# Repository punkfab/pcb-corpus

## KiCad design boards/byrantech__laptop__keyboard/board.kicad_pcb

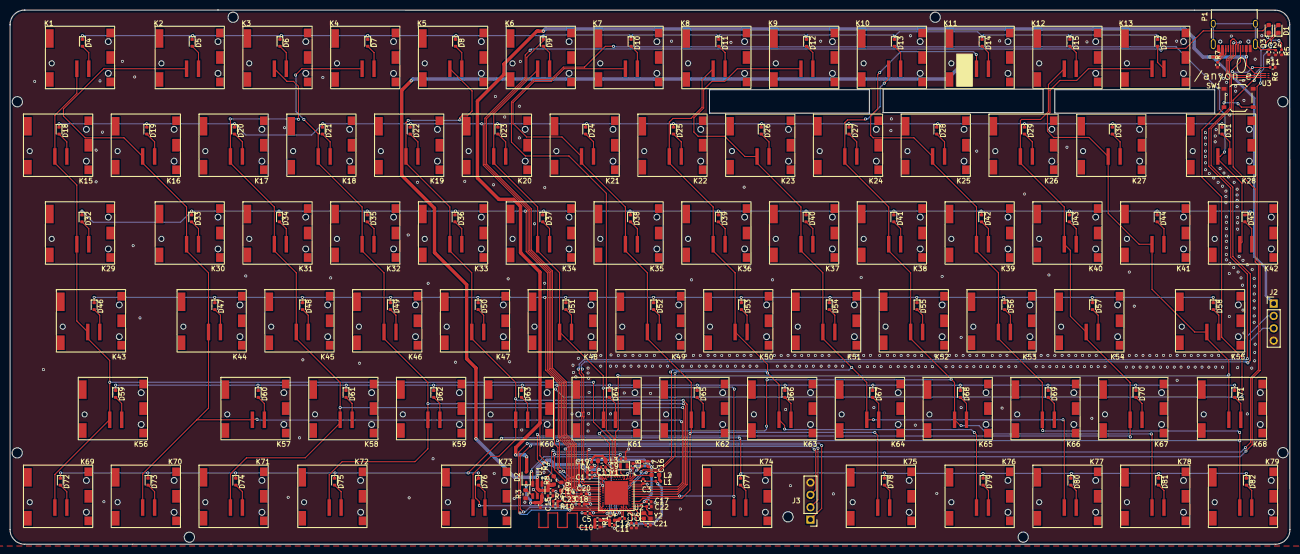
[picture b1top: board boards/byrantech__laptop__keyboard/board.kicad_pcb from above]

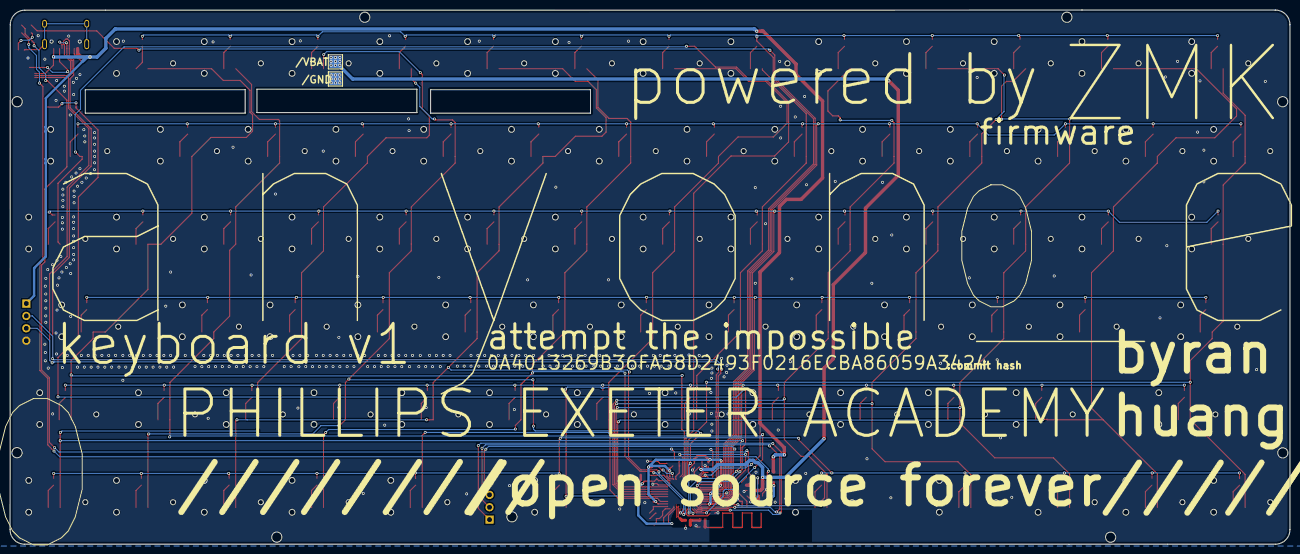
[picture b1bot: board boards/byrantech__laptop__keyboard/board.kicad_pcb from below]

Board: 2 copper layers, 262.5 x 109.5 mm, 220 parts (2 on the bottom side), 136 nets.

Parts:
AE1: Antenna; 2.4GHz-meander-antenna-v2
C1, C4, C13, C19: 4.7uF; C_0402_1005Metric
C2, C14, C15, C20: 1uF; C_0402_1005Metric
C3: 47nF; C_0402_1005Metric
C5: 1nF; C_0402_1005Metric
C6: 100pF; C_0402_1005Metric
C7, C16, C17, C18: 100nF; C_0402_1005Metric
C8, C9, C21, C22: 15pF; C_0402_1005Metric
C10: 1.5pF; C_0402_1005Metric
C11, C12: 1pF; C_0402_1005Metric
C23: 10nF; C_0402_1005Metric
C24: 1000pF/NC; C_0402_1005Metric
D1: CHG; LED_0603_1608Metric
D2: B5819W SL; D_SOD-323
D3: BLUE; LED_0603_1608Metric
D4, D5, D6, D7, D8, D9, D10, D11, D12, D13, D14, D15, D16, D18, D19, D20, D21, D22, D23, D24, D25, D26, D27, D28, D29, D30, D31, D32, D33, D34, D35, D36, D37, D38, D39, D40, D41, D42, D43, D44, D45, D46, D47, D48, D49, D50, D51, D52, D53, D54, D55, D56, D57, D58, D59, D60, D61, D62, D63, D64, D65, D66, D67, D68, D69, D70, D71, D72, D73, D74, D75, D76, D77, D78, D79, D80, D81, D82: D; D_SOD-523
H9, H10, H11, H13, H14, H16, H18, H20, H21: M2; M2_No_Padding
J2: USB POGO; PinHeader_1x04_P2.54mm_Vertical
J3: Debug; PinHeader_1x04_P2.54mm_Vertical
K1: Esc; Cherry_ULP_SMD
K2: F1; Cherry_ULP_SMD
K3: F2; Cherry_ULP_SMD
K4: F3; Cherry_ULP_SMD
K5: F4; Cherry_ULP_SMD
K6: F5; Cherry_ULP_SMD
K7: F6; Cherry_ULP_SMD
K8: F7; Cherry_ULP_SMD
K9: F8; Cherry_ULP_SMD
K10: F9; Cherry_ULP_SMD
K11: F10; Cherry_ULP_SMD
K12: F11; Cherry_ULP_SMD
K13: F12; Cherry_ULP_SMD
K15: ~~,`; Cherry_ULP_SMD
K16: !,1; Cherry_ULP_SMD
K17: @,2; Cherry_ULP_SMD
K18: #,3; Cherry_ULP_SMD
K19: $,4; Cherry_ULP_SMD
K20: %,5; Cherry_ULP_SMD
K21: ^,6; Cherry_ULP_SMD
K22: &,7; Cherry_ULP_SMD
K23: *,8; Cherry_ULP_SMD
K24: (,9; Cherry_ULP_SMD
K25: ),0; Cherry_ULP_SMD
K26: _,-; Cherry_ULP_SMD
K27: +,=; Cherry_ULP_SMD
K28: Backspace; Cherry_ULP_SMD
K29: Tab; Cherry_ULP_SMD
K30: Q; Cherry_ULP_SMD
K31: W; Cherry_ULP_SMD
K32: E; Cherry_ULP_SMD
K33: R; Cherry_ULP_SMD
K34: T; Cherry_ULP_SMD
K35: Y; Cherry_ULP_SMD
K36: U; Cherry_ULP_SMD
K37: I; Cherry_ULP_SMD
K38: O; Cherry_ULP_SMD
K39: P; Cherry_ULP_SMD
K40: {,[; Cherry_ULP_SMD
K41: },]; Cherry_ULP_SMD
K42: |,\; Cherry_ULP_SMD
K43: Caps Lock; Cherry_ULP_SMD
K44: A; Cherry_ULP_SMD
K45: S; Cherry_ULP_SMD
K46: D; Cherry_ULP_SMD
K47: F; Cherry_ULP_SMD
K48: G; Cherry_ULP_SMD
K49: H; Cherry_ULP_SMD
K50: J; Cherry_ULP_SMD
K51: K; Cherry_ULP_SMD
K52: L; Cherry_ULP_SMD
K53: :,;; Cherry_ULP_SMD
K54: ",'; Cherry_ULP_SMD
K55: Enter; Cherry_ULP_SMD
K56, K68: Shift; Cherry_ULP_SMD
K57: Z; Cherry_ULP_SMD
K58: X; Cherry_ULP_SMD
K59: C; Cherry_ULP_SMD
K60: V; Cherry_ULP_SMD
K61: B; Cherry_ULP_SMD
K62: N; Cherry_ULP_SMD
K63: M; Cherry_ULP_SMD
K64: <,,; Cherry_ULP_SMD
K65: >,.; Cherry_ULP_SMD
K66: ?,/; Cherry_ULP_SMD
K67: ↑; Cherry_ULP_SMD
K69: Fn; Cherry_ULP_SMD
K70: Ctrl; Cherry_ULP_SMD
K71, K76: Alt; Cherry_ULP_SMD
K72, K75: Meta; Cherry_ULP_SMD
K73, K74: Space; Cherry_ULP_SMD
K77: ←; Cherry_ULP_SMD
K78: ↓; Cherry_ULP_SMD
K79: →; Cherry_ULP_SMD
L1: 15nH; L_0402_1005Metric
L2, L3: 10uH; L_0603_1608Metric
L4: 3.9nH; L_0402_1005Metric
NT1: NetTie_2; net-tie-2-tiny
P1: USB-C; USB_C_Receptacle_HRO_TYPE-C-31-M-12
R1: 0R; R_0402_1005Metric
R2, R4: 10k; R_0402_1005Metric
R3: 2.7k; R_0603_1608Metric
R5: 1.5k; R_0402_1005Metric
R6, R7: 5.1k; R_0402_1005Metric
R8, R9: 2M; R_0603_1608Metric
R10: 10M; R_0402_1005Metric
R11: 1M; R_0402_1005Metric
SW1: Reset; SW_Push_1P1T_XKB_TS-1187A
TP5: VBAT; TestPoint_Pad_2.5x2.5mm
TP6: BAT GND; TestPoint_Pad_2.5x2.5mm
U1: BQ21040DBVR; SOT95P280X145-6N
U2: nRF52840; Nordic_AQFN-73-1EP_7x7mm_P0.5mm
U3: ESDR0502NMUTAG; UDFN-6_1.2x1.0mm_P0.4mm
Y1: 32.768 kHz; Crystal_SMD_2012-2Pin_2.0x1.2mm
Y2: 32MHz; Crystal_SMD_2016-4Pin_2.0x1.6mm

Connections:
/Key Matrix/Col_0: K1.1, K15.1, K29.1, K43.1, K56.1, K69.1, U2.U1 (TRACEDATA1/P0.12)
/Key Matrix/Col_1: K2.1, K16.1, K30.1, K44.1, K57.1, K70.1, U2.A8 (AIN7/P0.31)
/Key Matrix/Col_2: K3.1, K17.1, K31.1, K45.1, K58.1, K71.1, U2.A10 (AIN5/P0.29)
/Key Matrix/Col_3: K4.1, K18.1, K32.1, K46.1, K59.1, K72.1, U2.A12 (AIN0/P0.02)
/Key Matrix/Col_4: K5.1, K19.1, K33.1, K47.1, K60.1, K73.1, U2.A14 (P1.15)
/Key Matrix/Col_5: K6.1, K20.1, K34.1, K48.1, K61.1, K74.1, U2.A16 (P1.13)
/Key Matrix/Col_6: K7.1, K21.1, K35.1, K49.1, K62.1, K75.1, U2.A20 (P1.10)
/Key Matrix/Col_7: K8.1, K22.1, K36.1, K50.1, K63.1, K76.1, U2.J24 (NFC2/P0.10)
/Key Matrix/Col_8: K9.1, K23.1, K37.1, K51.1, K64.1, K77.1, U2.L24 (NFC1/P0.09)
/Key Matrix/Col_9: K10.1, K24.1, K38.1, K52.1, K65.1, K78.1, U2.R24 (P1.06)
/Key Matrix/Col_10: K11.1, K25.1, K39.1, K53.1, K66.1, K79.1, U2.U24 (P1.04)
/Key Matrix/Col_11: K12.1, K26.1, K40.1, K54.1, K67.1, U2.W24 (P1.02)
/Key Matrix/Col_12: K13.1, K27.1, K41.1, K55.1, K68.1, U2.L1 (P0.06)
/Key Matrix/Col_13: K28.1, K42.1, U2.N1 (P0.08)
/Key Matrix/Row_0: D4.1 (K), D5.1 (K), D6.1 (K), D7.1 (K), D8.1 (K), D9.1 (K), D10.1 (K), D11.1 (K), D12.1 (K), D13.1 (K), D14.1 (K), D15.1 (K), D16.1 (K), U2.AD8 (P0.13)
/Key Matrix/Row_1: D18.1 (K), D19.1 (K), D20.1 (K), D21.1 (K), D22.1 (K), D23.1 (K), D24.1 (K), D25.1 (K), D26.1 (K), D27.1 (K), D28.1 (K), D29.1 (K), D30.1 (K), D31.1 (K), U2.AD12 (P0.17)
/Key Matrix/Row_2: D32.1 (K), D33.1 (K), D34.1 (K), D35.1 (K), D36.1 (K), D37.1 (K), D38.1 (K), D39.1 (K), D40.1 (K), D41.1 (K), D42.1 (K), D43.1 (K), D44.1 (K), D45.1 (K), U2.AD16 (P0.20)
/Key Matrix/Row_3: D46.1 (K), D47.1 (K), D48.1 (K), D49.1 (K), D50.1 (K), D51.1 (K), D52.1 (K), D53.1 (K), D54.1 (K), D55.1 (K), D56.1 (K), D57.1 (K), D58.1 (K), U2.AD18 (P0.22)
/Key Matrix/Row_4: D59.1 (K), D60.1 (K), D61.1 (K), D62.1 (K), D63.1 (K), D64.1 (K), D65.1 (K), D66.1 (K), D67.1 (K), D68.1 (K), D69.1 (K), D70.1 (K), D71.1 (K), U2.AD20 (P0.24)
/Key Matrix/Row_5: D72.1 (K), D73.1 (K), D74.1 (K), D75.1 (K), D76.1 (K), D77.1 (K), D78.1 (K), D79.1 (K), D80.1 (K), D81.1 (K), D82.1 (K), U2.AC21 (P0.25)
/nRF52840/ANT: AE1.1 (A), C10.2, R1.2
/nRF52840/CC1: P1.A5 (CC), R6.1
/nRF52840/CC2: P1.B5 (VCONN), R7.1
BAT_VOLT: C23.2, R9.2, R10.1, U2.J1 (AIN2/P0.04)
BLUE_LED: D3.2 (A), U2.AD10 (P0.15)
GND: C1.1, C2.1, C3.1, C4.2, C5.2, C6.2, C7.2, C8.1, C9.1, C10.1, C11.1, C13.1, C14.2, C15.2, C16.1, C17.1, C18.1, C19.1, C20.1, C21.2, C22.2, C23.1, C24.2, J2.4, J3.4, NT1.2, P1.A1 (GND), P1.A12 (GND), P1.B1 (GND), P1.B12 (GND), R3.1, R4.1, R5.1, R6.2, R7.2, R10.2, R11.1, SW1.2, TP6.1, U1.5 (GND), U2.B7 (VSS), U2.EP (VSS), U3.1 (GND), Y2.2, Y2.4
unnamed: C11.2, L4.1, R1.1
unnamed: D1.2 (A), R2.2
unnamed: D1.1 (K), U1.3 (~CHG)
unnamed: C15.1, D2.1 (K), U1.6 (VIN)
unnamed: D3.1 (K), R5.2
unnamed: D4.2 (A), K1.2
unnamed: D5.2 (A), K2.2
unnamed: D6.2 (A), K3.2
unnamed: D7.2 (A), K4.2
unnamed: D8.2 (A), K5.2
unnamed: D9.2 (A), K6.2
unnamed: D10.2 (A), K7.2
unnamed: D11.2 (A), K8.2
unnamed: D12.2 (A), K9.2
unnamed: D13.2 (A), K10.2
unnamed: D14.2 (A), K11.2
unnamed: D15.2 (A), K12.2
unnamed: D16.2 (A), K13.2
unnamed: D18.2 (A), K15.2
unnamed: D19.2 (A), K16.2
unnamed: D20.2 (A), K17.2
unnamed: D21.2 (A), K18.2
unnamed: D22.2 (A), K19.2
unnamed: D23.2 (A), K20.2
unnamed: D24.2 (A), K21.2
unnamed: D25.2 (A), K22.2
unnamed: D26.2 (A), K23.2
unnamed: D27.2 (A), K24.2
unnamed: D28.2 (A), K25.2
unnamed: D29.2 (A), K26.2
unnamed: D30.2 (A), K27.2
unnamed: D31.2 (A), K28.2
unnamed: D32.2 (A), K29.2
unnamed: D33.2 (A), K30.2
unnamed: D34.2 (A), K31.2
unnamed: D35.2 (A), K32.2
unnamed: D36.2 (A), K33.2
unnamed: D37.2 (A), K34.2
unnamed: D38.2 (A), K35.2
unnamed: D39.2 (A), K36.2
unnamed: D40.2 (A), K37.2
unnamed: D41.2 (A), K38.2
unnamed: D42.2 (A), K39.2
unnamed: D43.2 (A), K40.2
unnamed: D44.2 (A), K41.2
unnamed: D45.2 (A), K42.2
unnamed: D46.2 (A), K43.2
unnamed: D47.2 (A), K44.2
unnamed: D48.2 (A), K45.2
unnamed: D49.2 (A), K46.2
unnamed: D50.2 (A), K47.2
unnamed: D51.2 (A), K48.2
unnamed: D52.2 (A), K49.2
unnamed: D53.2 (A), K50.2
unnamed: D54.2 (A), K51.2
unnamed: D55.2 (A), K52.2
unnamed: D56.2 (A), K53.2
unnamed: D57.2 (A), K54.2
unnamed: D58.2 (A), K55.2
unnamed: D59.2 (A), K56.2
unnamed: D60.2 (A), K57.2
unnamed: D61.2 (A), K58.2
unnamed: D62.2 (A), K59.2
unnamed: D63.2 (A), K60.2
unnamed: D64.2 (A), K61.2
unnamed: D65.2 (A), K62.2
unnamed: D66.2 (A), K63.2
unnamed: D67.2 (A), K64.2
unnamed: D68.2 (A), K65.2
unnamed: D69.2 (A), K66.2
unnamed: D70.2 (A), K67.2
unnamed: D71.2 (A), K68.2
unnamed: D72.2 (A), K69.2
unnamed: D73.2 (A), K70.2
unnamed: D74.2 (A), K71.2
unnamed: D75.2 (A), K72.2
unnamed: D76.2 (A), K73.2
unnamed: D77.2 (A), K74.2
unnamed: D78.2 (A), K75.2
unnamed: D79.2 (A), K76.2
unnamed: D80.2 (A), K77.2
unnamed: D81.2 (A), K78.2
unnamed: D82.2 (A), K79.2
unnamed: L1.2, L2.1
unnamed: C24.1, P1.S1 (SHIELD), R11.2
unnamed: R8.2, R9.1
unnamed: R3.2, U1.4 (ISET)
unnamed: R4.2, U1.1 (TS)
unnamed: C12.2, L4.2, U2.H23 (ANT)
unnamed: L2.2, U2.B3 (DCC)
unnamed: L3.2, U2.AB2 (DCCH)
unnamed: C7.1, U2.C1 (DEC1)
unnamed: C6.1, U2.D23 (DEC3)
unnamed: C2.2, C3.2, L1.1, U2.B5 (DEC4), U2.E24 (DEC6)
unnamed: C5.1, U2.N24 (DEC5)
unnamed: C4.1, U2.AC5 (DECUSB)
unnamed: C21.1, U2.B24 (XC1), Y2.1
unnamed: C22.1, U2.A23 (XC2), Y2.3
unnamed: C8.2, U2.D2 (XL1/P0.00), Y1.1
unnamed: C9.2, U2.F2 (XL2/P0.01), Y1.2
RESET: SW1.1, U2.AC9 (P0.14), U2.AC11 (P0.16), U2.AC13 (P0.18/~RESET)
SWC: J3.1, U2.AA24 (SWDCLK)
SWD: J3.2, U2.AC24 (SWDIO)
SWO: J3.3, U2.AD22 (TRACEDATA0/P1.00)
USB_D+: J2.2, P1.A6 (D+), P1.B6 (D+), U2.AD6 (D+), U3.5 (D+)
USB_D-: J2.3, P1.A7 (D-), P1.B7 (D-), U2.AD4 (D-), U3.6 (VBUS)
VBAT: C13.2, C14.1, R2.1, R8.1, TP5.1, U1.2 (OUT), U2.Y2 (VDDH)
VBUS: C1.2, D2.2 (A), J2.1, P1.A4 (VBUS), P1.A9 (VBUS), P1.B4 (VBUS), P1.B9 (VBUS), U2.AD2 (VBUS), U3.4 (D-)
VDD_NRF: C16.2, C17.2, C18.2, C19.2, C20.2, L3.1, U2.A22 (VDD), U2.AD14 (VDD), U2.AD23 (VDD), U2.B1 (VDD), U2.W1 (VDD)
VSS_PA: C12.1, NT1.1, U2.F23 (VSS_PA)

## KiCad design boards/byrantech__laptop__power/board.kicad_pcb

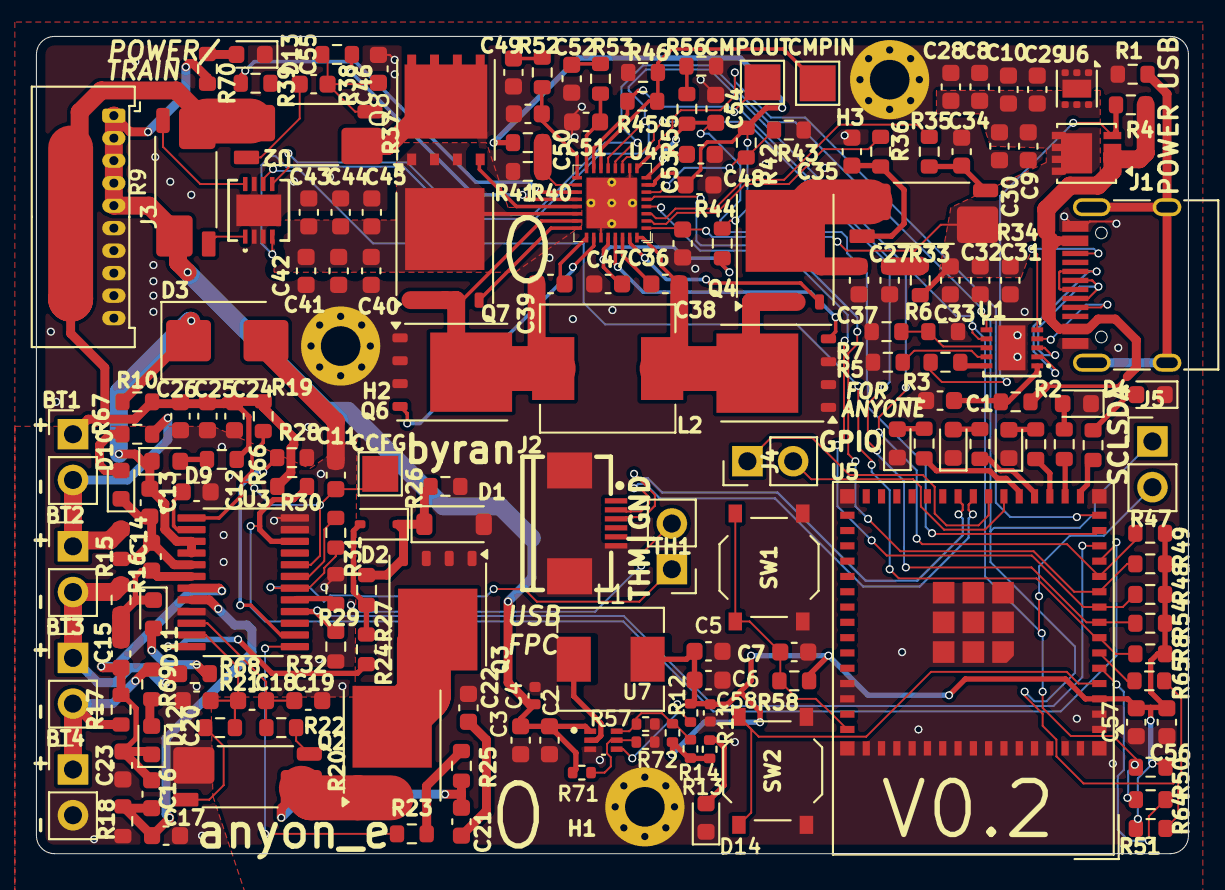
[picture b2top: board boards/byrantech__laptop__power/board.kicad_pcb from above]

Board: 13 copper layers, 64.0 x 45.4 mm, 179 parts (0 on the bottom side), 115 nets.

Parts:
BT1: Cell 1; PinHeader_1x02_P2.54mm_Vertical
BT2: Cell 2; PinHeader_1x02_P2.54mm_Vertical
BT3: Cell 3; PinHeader_1x02_P2.54mm_Vertical
BT4: Cell 4; PinHeader_1x02_P2.54mm_Vertical
C1, C7, C11, C12, C13, C14, C15, C16, C17, C23, C27, C46, C48: 1uF; C_0603_1608Metric
C2, C3, C8, C9, C24, C25, C28, C29, C30, C31, C32, C33, C40, C41, C42, C43, C44, C45, C56: 10uF; C_0603_1608Metric
C4, C58: 100nF; C_0402_1005Metric
C5, C6: 22uF; C_0603_1608Metric
C10, C26: 100nF; C_0603_1608Metric
C18, C19, C20, C21, C22, C55, C57: 0.1uF; C_0603_1608Metric
C34, C35: 33nF; C_0603_1608Metric
C36: 470nF; C_0603_1608Metric
C37: 10nF; C_0603_1608Metric
C38, C39: 47nF; C_0603_1608Metric
C47: 2.2uF; C_0603_1608Metric
C49: 680pF; C_0603_1608Metric
C50: 15pF; C_0603_1608Metric
C51: 33pF; C_0603_1608Metric
C52: 1800pF; C_0603_1608Metric
C53, C54: 100pF; C_0603_1608Metric
D1: MMSZ5248B; D_SOD-123
D2: BAS316; D_SOD-323
D3: SMBJ26A-13-F; D_SMB
D4: LED1; LED_0603_1608Metric
D5: LED2; LED_0603_1608Metric
D6: LED3; LED_0603_1608Metric
D7: LED4; LED_0603_1608Metric
D8: LED5; LED_0603_1608Metric
D9: C4 LED; LED_0603_1608Metric
D10: C3 LED; LED_0603_1608Metric
D11: C2 LED; LED_0603_1608Metric
D12: C1 LED; LED_0603_1608Metric
D13: VDD LED; LED_0603_1608Metric
D14: +3.3V LED; LED_0603_1608Metric
H1, H2, H3: M2; MountingHole_2.2mm_M2_Pad_Via
J1: USB-C Power + USB2.0; USB_C_Receptacle_HRO_TYPE-C-31-M-12
J2: USB; FPC-SMD_6P-P0.50_XUNPU_FPC-05F-6PH20
J3: BATTERY OUT; Molex_PicoBlade_53048-1010_1x10_P1.25mm_Horizontal
J4: BACKUP; PinHeader_1x02_P2.54mm_Vertical
J5: I2C; PinHeader_1x02_P2.54mm_Vertical
L1: MWSA0503S-3R3MT; L_Sunlord_MWSA0503S
L2: MWSA0603S-2R2MT; L_Sunlord_MWSA0603S
Q1: SI7617DN-T1-GE3; Vishay_PowerPAK_1212-8_Single
Q2, Q3, Q4, Q5, Q6, Q7: CSD18534Q5A; TDSON-8-1
Q8: AON6411; AO_DFN-8-1EP_5.55x5.2mm_P1.27mm_EP4.12x4.6mm
R1, R27: 1M; R_0603_1608Metric
R2, R38, R39, R44: 10R; R_0603_1608Metric
R3, R23, R24: 5.1k; R_0603_1608Metric
R4: 49.9k; R_0603_1608Metric
R5, R6: DNP; R_0603_1608Metric
R7, R64, R65: 0R; R_0603_1608Metric
R8: 2.2k; R_0603_1608Metric
R9, R34, R37: 10mΩ SHUNT FMF25FPJR010-LH; R_Shunt_Vishay_WSK2512_6332Metric_T1.19mm
R10, R15, R16, R17, R18: 33R; R_0603_1608Metric
R11, R71: 47k; R_0402_1005Metric
R12, R57: 10k; R_0402_1005Metric
R13: 49.9k; R_0402_1005Metric
R14: 510k; R_0402_1005Metric
R19, R66, R67, R68, R69, R70: 1k; R_0603_1608Metric
R20: 15mΩ SHUNT RLP25FEER015; R_Shunt_Vishay_WSK2512_6332Metric_T1.19mm
R21, R22: 100R; R_0603_1608Metric
R25: 10M; R_0603_1608Metric
R26: 3M; R_0603_1608Metric
R28, R41: 470k; R_0603_1608Metric
R29: 100k; R_0603_1608Metric
R30, R31, R32, R47, R48, R49, R50, R51, R52, R58, R59, R60, R61, R62, R63: 10k; R_0603_1608Metric
R33: 2.2R; R_0603_1608Metric
R35, R36: 5.1R; R_0603_1608Metric
R40: 130k; R_0603_1608Metric
R42: 390k; R_0603_1608Metric
R43: 220k; R_0603_1608Metric
R45: 2M; R_0603_1608Metric
R46: 300k; R_0603_1608Metric
R53: 40.2k; R_0603_1608Metric
R54: 200R; R_0603_1608Metric
R55: 110k; R_0603_1608Metric
R56: 27k; R_0603_1608Metric
R72: 12k; R_0402_1005Metric
SW1: RST; SW_Push_1P1T_XKB_TS-1187A
SW2: BOOT; SW_Push_1P1T_XKB_TS-1187A
TH1: 103AT 10k; PinHeader_1x02_P2.54mm_Vertical
TP1: CCFG; TestPoint_Pad_2.0x2.0mm
TP2: CMPIN; TestPoint_Pad_2.0x2.0mm
TP3: CMPOUT; TestPoint_Pad_2.0x2.0mm
U1: HUSB238; DFN-10_L3.0-W3.0-P0.50-BL-EP2.5
U2: LTC2943; DFN-8_DD_LIT
U3: BQ7791501PWR; SOP65P640X120-24N
U4: BQ25713RSNR; RSN0032B
U5: ESP32-S3-MINI-1; ESP32-S2-MINI-1
U6: TVS2200DRV; WSON-6-1EP_2x2mm_P0.65mm_EP1x1.6mm
U7: TPS564257DRLR; SOT50P160X60-6N

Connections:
+3.3V: C5.1, C6.1, C56.2, C57.2, C58.1, L1.2, R8.2, R11.2, R12.2, R13.2, R14.2, R47.2, R48.2, R49.2, R50.2, R51.2, R54.2, R58.2, U5.3 (3V3)
/3V3_SW: L1.1, U7.2 (SW)
/BATDRV_N: Q8.4 (G), U4.21 (BATDRV_N)
/BMS_SRN: C18.1, C20.1, R21.2, U3.11 (SRN)
/BMS_SRP: C18.2, C19.1, R22.2, U3.10 (SRP)
/BTST1: C38.2, U4.30 (BTST1)
/BTST2: C39.2, U4.25 (BTST2)
/C1: BT3.2 (-), BT4.1 (+), R17.1, R69.1
/C2: BT2.2 (-), BT3.1 (+), R16.1, R68.1
/C3: BT1.2 (-), BT2.1 (+), R15.1, R67.1
/C4: BT1.1 (+), C24.1, C25.1, C26.1, R9.4, R10.1, R19.1, R30.2, R37.1, R66.1
/CBI: R32.1, U3.16 (CBI), U5.13 (IO9)
/CC1: J1.A5 (CC1), U1.4 (CC1)
/CC2: J1.B5 (CC2), U1.5 (CC2)
/CELL_BATPRES: R40.1, R41.2, U4.18 (CELL_BATPRES)
/CHG: Q2.4 (G), R23.2, R25.2
/CHRG_OK: R48.1, U4.4 (CHRG_OK), U5.9 (IO5)
/CMPOUT: R45.2, R47.1, TP3.1, U4.15 (CMPOUT), U5.11 (IO7)
/COMP1: C51.1, R53.2, U4.16 (COMP1)
/COMP2: C50.1, R52.2, U4.17 (COMP2)
/D+: J1.A6 (D+), J1.B6 (D+), U1.2 (D+)
/D-: J1.A7 (D-), J1.B7 (D-), U1.3 (D-)
/DSG: D1.1 (K), D2.1 (K), Q3.4 (G), R26.2, R27.2
/EN: C7.2, R58.1, SW1.1 (A), U5.45 (EN)
/EN_OTG: R49.1, U4.5 (EN_OTG), U5.10 (IO6)
/HIDRV1: Q4.4 (G), U4.31 (HIDRV1)
/HIDRV2: Q7.4 (G), U4.24 (HIDRV2)
/IADPT: C54.2, R55.2, U4.8 (IADPT), U5.14 (IO10)
/IBAT: C53.2, U4.9 (IBAT), U5.15 (IO11)
/ILIM_HIZ: R42.1, R43.2, U4.6 (ILIM_HIZ)
/IO0: SW2.1 (A), U5.4 (IO0)
/LD: R28.2, U3.14 (LD)
/LED1: R59.1, U5.16 (IO12)
/LED2: R60.1, U5.17 (IO13)
/LED3: R61.1, U5.18 (IO14)
/LED4: R62.1, U5.19 (IO15)
/LED5: R63.1, U5.20 (IO16)
/LODRV1: Q5.4 (G), U4.29 (LODRV1)
/LODRV2: Q6.4 (G), U4.26 (LODRV2)
/PRES: R30.1, U3.22 (PRES), U5.12 (IO8)
/PROCHOT_N: R54.1, U4.11 (PROCHOT_N), U5.8 (IO4)
/REGN: C47.1, R44.2, U4.28 (REGN)
/SCL: J5.2, R50.1, R64.2, U1.7 (SCL), U2.4 (SCL), U4.13 (SCL)
/SDA: J5.1, R51.1, R65.2, U1.6 (SDA), U2.5 (SDA), U4.12 (SDA)
/SRN: R39.1, U4.19 (SRN)
/SRP: R38.1, U4.20 (SRP)
/SW1: C38.1, L2.1, Q4.1 (S), Q4.2 (S), Q4.3 (S), Q5.5 (D), U4.32 (SW1)
/SW2: C39.1, L2.2, Q6.5 (D), Q7.1 (S), Q7.2 (S), Q7.3 (S), U4.23 (SW2)
/USB_D+: J2.3, U5.24 (IO20)
/USB_D-: J2.2, U5.23 (IO19)
/VBUS: C8.1, C9.1, C10.1, C28.1, C29.1, C30.1, C31.1, C32.1, C33.1, C36.1, Q1.5 (D), R33.2, R34.4, U4.1 (VBUS), U6.4 (IN), U6.5 (IN), U6.6 (IN)
/VC0: C16.2, C17.1, R18.2, U3.8 (VC0)
/VC1: C15.2, C16.1, C23.1, D12.1 (K), R17.2, U3.7 (VC1)
/VC2: C14.2, C15.1, D11.1 (K), R16.2, U3.6 (VC2)
/VC3: C13.2, C14.1, D10.1 (K), R15.2, U3.5 (VC3)
/VC4: C13.1, D3.1 (A1), D9.1 (K), R10.2, U3.3 (VC5), U3.4 (VC4)
/VDDA: C48.1, R40.2, R42.2, R44.1, U4.7 (VDDA)
/VSYS: C40.1, C41.1, C42.1, C43.1, C44.1, C45.1, Q7.5 (D), Q8.1 (S), Q8.2 (S), Q8.3 (S), U4.22 (VSYS)
/~ALCC: R8.1, U2.6 (*ALCC), U5.7 (IO3)
GND: C1.2, C2.2, C3.2, C4.2, C5.2, C6.2, C7.1, C8.2, C9.2, C10.2, C22.2, C27.2, C28.2, C29.2, C30.2, C31.2, C32.2, C33.2, C34.2, C35.2, C36.2, C37.2, C40.2, C41.2, C42.2, C43.2, C44.2, C45.2, C46.2, C47.2, C48.2, C49.2, C50.2, C51.2, C52.2, C53.1, C54.1, C56.1, C57.1, C58.2, D1.2 (A), D4.1 (K), D5.1 (K), D6.1 (K), D7.1 (K), D8.1 (K), D13.1 (K), D14.1 (K), H1.1, H2.1, H3.1, J1.A1 (GND), J1.A12 (GND), J1.B1 (GND), J1.B12 (GND), J2.6, J2.MP (MountPin), J3.6, J3.7, J3.8, J3.9, J3.10, Q3.1 (S), Q3.2 (S), Q3.3 (S), Q5.1 (S), Q5.2 (S), Q5.3 (S), Q6.1 (S), Q6.2 (S), Q6.3 (S), R1.2, R5.2, R6.2, R7.2, R26.1, R28.1, R41.1, R43.1, R46.1, R56.1, R57.1, R72.1, SW1.2 (B), SW2.2 (B), U1.11 (GND), U2.2 (GND), U2.3 (GND), U2.7 (GND), U2.9 (EPAD), U4.10 (PSYS), U4.27 (PGND), U4.33 (PAD), U5.1 (GND), U5.2 (GND), U5.42 (GND), U5.43 (GND), U5.46 (GND), U5.47 (GND), U5.48 (GND), U5.49 (GND), U5.50 (GND), U5.51 (GND), U5.52 (GND), U5.53 (GND), U5.54 (GND), U5.55 (GND), U5.56 (GND), U5.57 (GND), U5.58 (GND), U5.59 (GND), U5.60 (GND), U5.61 (GND), U5.62 (GND), U5.63 (GND), U5.64 (GND), U5.65 (GND), U6.1 (GND), U6.2 (GND), U6.3 (GND), U6.7 (GND), U7.3 (GND)
GNDPWR: BT4.2 (-), C11.2, C12.2, C17.2, C19.2, C20.2, C23.2, C24.2, C25.2, C26.2, D3.2 (A2), R18.1, R20.1, R29.2, R32.2, TH1.2, U3.9 (VSS), U3.23 (CTRC), U3.24 (CTRD)
unnamed: C21.1, Q2.1 (S), Q2.2 (S), Q2.3 (S), R20.4, R25.1
unnamed: C21.2, C22.1
unnamed: C27.1, R33.1
unnamed: C34.1, R34.3, R35.2
unnamed: C35.1, R34.2, R36.2
unnamed: C46.1, C55.1, R37.3, R38.2
unnamed: C49.1, R52.1
unnamed: C52.1, R53.1
unnamed: C55.2, R37.2, R39.2
unnamed: D2.2 (A), R24.2, R27.1
unnamed: D4.2 (A), R59.2
unnamed: D5.2 (A), R60.2
unnamed: D6.2 (A), R61.2
unnamed: D7.2 (A), R62.2
unnamed: D8.2 (A), R63.2
unnamed: D9.2 (A), R66.2
unnamed: D10.2 (A), R67.2
unnamed: D11.2 (A), R68.2
unnamed: D12.2 (A), R69.2
unnamed: D13.2 (A), R70.2
unnamed: D14.2 (A), R11.1
unnamed: J1.S1 (SHIELD), R1.1
unnamed: J1.A4 (VBUS), J1.A9 (VBUS), J1.B4 (VBUS), J1.B9 (VBUS), Q1.1 (S), Q1.2 (S), Q1.3 (S), R2.1, R4.2
unnamed: J4.1, U5.22 (IO18)
unnamed: J4.2, U5.21 (IO17)
unnamed: Q1.4 (G), R3.2, R4.1
unnamed: Q2.5 (D), Q3.5 (D)
unnamed: C37.1, Q4.5 (D), R34.1
unnamed: Q8.5 (D), R37.4
unnamed: R20.2, R21.1
unnamed: R20.3, R22.1
unnamed: R55.1, R56.2
unnamed: R3.1, U1.10 (GATE)
unnamed: R5.1, U1.9 (ISET)
unnamed: C1.1, R2.2, U1.1 (VIN)
unnamed: R6.1, R7.1, U1.8 (VSET)
unnamed: R9.2, U2.1 (SENSE+)
unnamed: R9.3, U2.8 (SENSE-)
unnamed: C12.1, U3.2 (AVDD)
unnamed: C11.1, R19.2, TP1.1, U3.1 (VDD), U3.20 (CCFG)
unnamed: R23.1, U3.13 (CHG)
unnamed: R24.1, U3.12 (DSG)
unnamed: R29.1, U3.17 (OCDP)
unnamed: R31.2, TH1.1, U3.18 (TS)
unnamed: R31.1, U3.19 (VTB)
unnamed: R36.1, U4.2 (ACN)
unnamed: R35.1, U4.3 (ACP)
unnamed: R45.1, R46.2, TP2.1, U4.14 (CMPIN)
unnamed: R64.1, U5.5 (IO1)
unnamed: R65.1, U5.6 (IO2)
unnamed: R71.1, R72.2, U7.5 (EN)
unnamed: R13.1, R14.1, R57.2, U7.6 (FB)
unnamed: R12.1, U7.4 (PG)
VDD: C2.1, C3.1, C4.1, J3.1, J3.2, J3.3, J3.4, J3.5, R9.1, R70.1, R71.2, U7.1 (VIN)

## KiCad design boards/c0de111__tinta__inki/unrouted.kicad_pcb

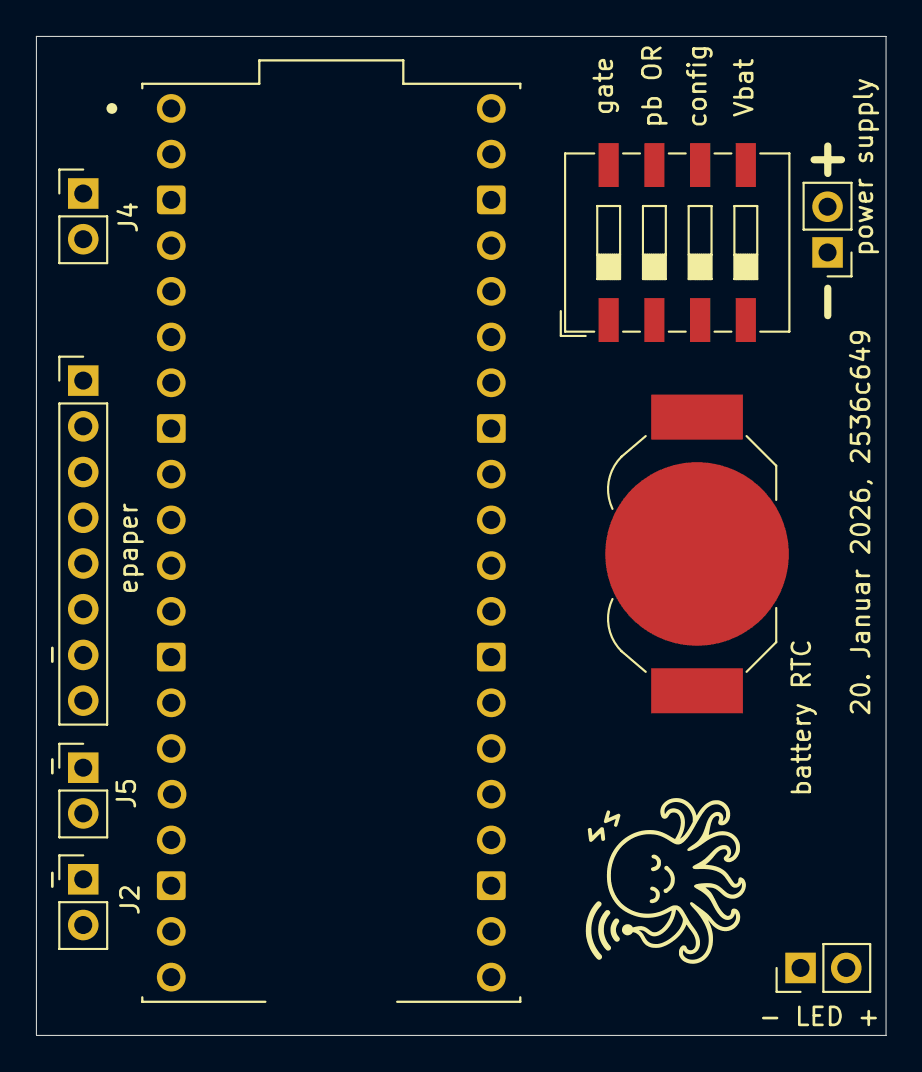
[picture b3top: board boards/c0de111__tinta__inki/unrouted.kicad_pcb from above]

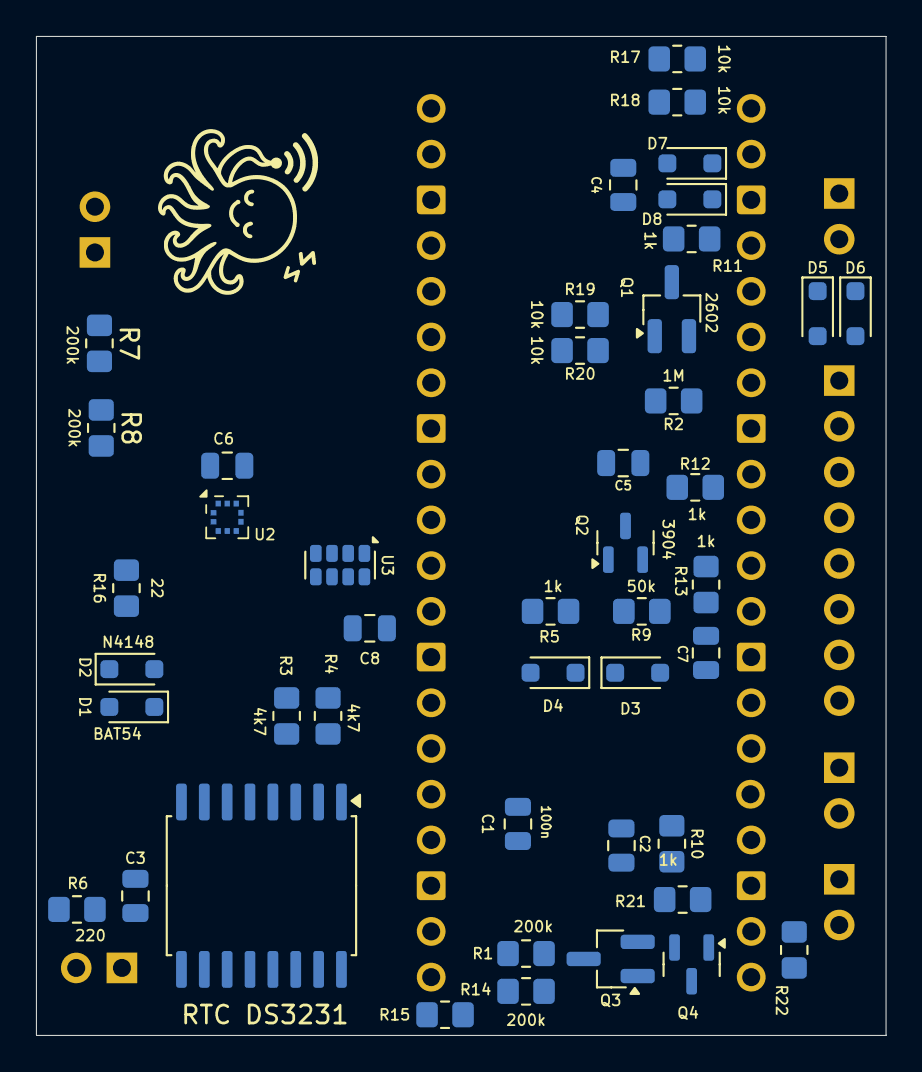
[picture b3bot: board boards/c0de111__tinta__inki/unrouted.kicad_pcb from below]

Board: 2 copper layers, 47.2 x 55.5 mm, 54 parts (45 on the bottom side), 44 nets, no tracks yet.

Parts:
C1, C2, C3, C4, C5, C6, C7, C8: 100nF; C_0805_2012Metric
D1, D3, D4, D5, D6, D7, D8: BAT54J; D_SOD-323_HandSoldering
D2: 1N4148WS; D_SOD-323_HandSoldering
J1: connector epaper; PinHeader_1x08_P2.54mm_Vertical
J2, J3, J4, J5, J7: Conn_01x02_Socket; PinHeader_1x02_P2.54mm_Vertical
Q1, Q3: TSM260P02CX; SOT-23_Handsoldering
Q2, Q4: MMBT3904; SOT-23
R1, R7, R8, R14: 200k; R_0805_2012Metric_Pad1.20x1.40mm_HandSolder
R2: 1M; R_0805_2012Metric_Pad1.20x1.40mm_HandSolder
R3, R4: 4k7; R_0805_2012Metric_Pad1.20x1.40mm_HandSolder
R5, R10, R11, R12, R13, R21: 1k; R_0805_2012Metric_Pad1.20x1.40mm_HandSolder
R6: 220R; R_0805_2012Metric_Pad1.20x1.40mm_HandSolder
R9, R22: 50k; R_0805_2012Metric_Pad1.20x1.40mm_HandSolder
R15: 2M2; R_0805_2012Metric_Pad1.20x1.40mm_HandSolder
R16: 22R; R_0805_2012Metric_Pad1.20x1.40mm_HandSolder
R17, R18, R19, R20: 10k; R_0805_2012Metric_Pad1.20x1.40mm_HandSolder
SW1: SW_DIP_x04; SW_DIP_SPSTx04_Slide_9.78x12.34mm_W8.61mm_P2.54mm
U1: DS3231M; SOIC-16W_7.5x10.3mm_P1.27mm
U2: BMP581
U3: RV-3028-C7; MicroCrystal_C7_SON-8_1.5x3.2mm_P0.9mm
battery_RTC1: Battery 3,7V; BatteryHolder_LINX_BAT-HLD-012-SMT
pico1: SC0918; MODULE_SC0918

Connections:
3V3: C1.1, C3.1, C6.1, C8.1, J1.8, R3.1, R4.1, SW1.6, U1.2 (VCC), U2.1 (VDDIO), U2.5 (SDO), U2.6 (CSB), U2.10 (VDD), U3.7 (VDD), pico1.36 (3V3_OUT)
/optional i2c devices/SCL: R4.2, U1.16 (SCL), U2.2 (SCK), U3.3 (SCL), pico1.27 (GP21)
/optional i2c devices/SDA: R3.2, U1.15 (SDA), U2.4 (SDI), U3.4 (SDA), pico1.26 (GP20)
GND: C1.2, C2.2, C3.2, C4.2, C5.2, C6.2, C7.2, C8.2, J1.7, J2.1, J3.1, J5.1, J7.1, Q2.2 (E), Q4.2 (E), R8.2, R9.2, R14.2, R22.1, U1.5 (GND), U1.6 (GND), U1.7 (GND), U1.8 (GND), U1.9 (GND), U1.10 (GND), U1.11 (GND), U1.12 (GND), U1.13 (GND), U2.3 (VSS), U2.7 (INT), U2.8 (VSS), U2.9 (VSS), U3.5 (VSS), battery_RTC1.2 (-), pico1.3 (GND), pico1.8 (GND), pico1.13 (GND), pico1.18 (GND), pico1.23 (GND), pico1.28 (GND), pico1.33 (AGND), pico1.38 (GND)
INT: J2.2, Q1.1 (G), R2.2, R10.2, SW1.7, SW1.8, U1.3 (~INT/SQW), U3.2 (~INT)
unnamed: C2.1, R10.1
unnamed: D1.2 (A), battery_RTC1.1 (+)
unnamed: D2.2 (A), R16.1
unnamed: C7.1, D3.2 (A), R13.2
unnamed: D3.1 (K), D4.1 (K), J5.2
unnamed: D4.2 (A), D5.2 (A), D7.2 (A), SW1.2
unnamed: D5.1 (K), D6.1 (K), J4.2
unnamed: C5.1, D6.2 (A), R12.2
unnamed: D7.1 (K), D8.1 (K), J4.1
unnamed: C4.1, D8.2 (A), R11.2
unnamed: J1.1, pico1.17 (GP13)
unnamed: J1.2, pico1.16 (GP12)
unnamed: J1.3, pico1.11 (GP8)
unnamed: J1.4, pico1.12 (GP9)
unnamed: J1.5, pico1.14 (GP10)
unnamed: J1.6, pico1.15 (GP11)
unnamed: J3.2, Q1.2 (S), R2.1, SW1.5
unnamed: J7.2, R6.2
unnamed: Q1.3 (D), R7.1, pico1.39 (VSYS)
unnamed: Q2.1 (B), R5.1
unnamed: Q2.3 (C), SW1.1
unnamed: Q3.3 (D), R1.1
unnamed: Q3.1 (G), Q4.3 (C), R15.2
unnamed: Q4.1 (B), R21.2
unnamed: R16.2, SW1.4
unnamed: R17.1, R18.1, R19.1, R20.1, SW1.3
unnamed: R17.2, pico1.1 (GP0)
unnamed: R18.2, pico1.2 (GP1)
unnamed: R19.2, pico1.4 (GP2)
unnamed: R20.2, pico1.5 (GP3)
unnamed: R11.1, pico1.7 (GP5)
unnamed: R12.1, pico1.9 (GP6)
unnamed: R13.1, pico1.10 (GP7)
unnamed: R21.1, R22.2, pico1.19 (GP14)
unnamed: R6.1, pico1.21 (GP16)
unnamed: R5.2, R9.1, pico1.29 (GP22)
unnamed: R7.2, R8.1, pico1.31 (GP26)
unnamed: R1.2, R14.1, pico1.32 (GP27)
Vbat: D1.1 (K), D2.1 (K), Q3.2 (S), R15.1, U1.14 (VBAT), U3.6 (VBACKUP)

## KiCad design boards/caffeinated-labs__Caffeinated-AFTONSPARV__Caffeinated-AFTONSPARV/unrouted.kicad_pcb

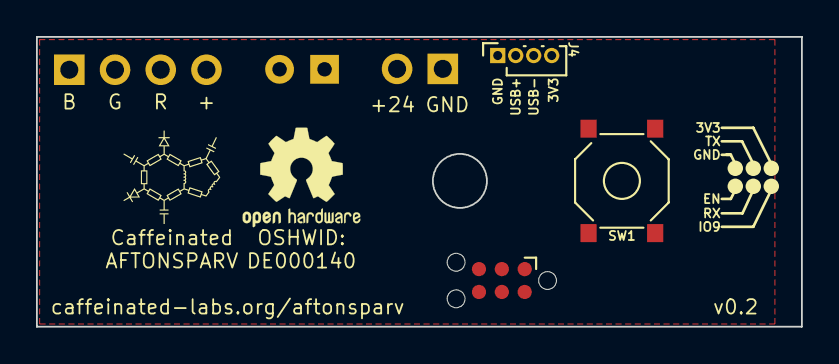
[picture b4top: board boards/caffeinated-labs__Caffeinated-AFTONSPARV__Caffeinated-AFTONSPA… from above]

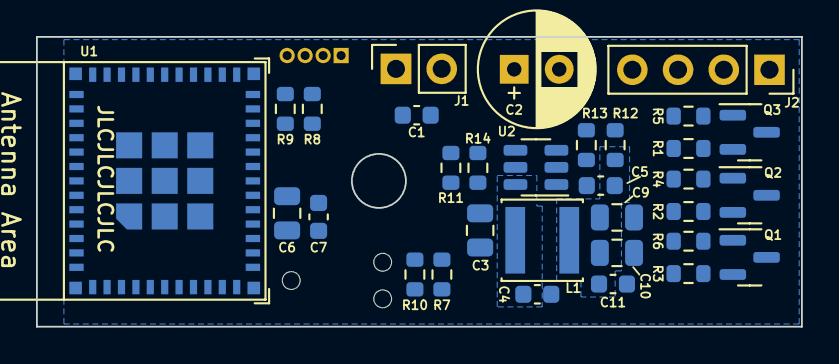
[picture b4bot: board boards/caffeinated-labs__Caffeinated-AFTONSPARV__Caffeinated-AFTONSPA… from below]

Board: 4 copper layers, 42.5 x 16.1 mm, 35 parts (32 on the bottom side), 25 nets, no tracks yet.

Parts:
C1, C4, C7, C11: 100nF; C_0603_1608Metric
C2: 100µF 35V; CP_Radial_D6.3mm_P2.50mm
C3, C6, C9, C10: 4.7uF; C_0805_2012Metric
C5: 22pF; C_0603_1608Metric
J1: PWR; PinSocket_1x02_P2.54mm_Vertical
J2: LED; PinSocket_1x04_P2.54mm_Vertical
J3: TagConnect; Tag-Connect_TC2030-IDC-NL_2x03_P1.27mm_Vertical
J4: USB; PinSocket_1x04_P1.00mm_Vertical
L1: 10uH; L_Sunlord_SWPA4030S
Q1, Q2, Q3: AO3400A; SOT-23
R1, R2, R3, R7, R8, R9, R10, R14: 10kΩ; R_0603_1608Metric
R4, R5, R6: 20Ω; R_0603_1608Metric
R11: 1Ω; R_0603_1608Metric
R12: 100kΩ; R_0603_1608Metric
R13: 22.1kΩ; R_0603_1608Metric
SW1: SW_Push; YTS-C005
U1: ESP32-C3-MINI-1-[H/N]4; ESP32-C3-MINI-1
U2: SY8201ABC; SOT-23-6

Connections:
+3.3V: C5.2, C6.1, C7.1, C9.1, C10.1, C11.1, J3.1 (VCC), J4.4, L1.2, R7.1, R8.1, R9.1, R10.1, R12.1, U1.3 (3V3)
+24V: C1.1, C2.1, J1.2, J2.4, R11.1
EN: J3.6 (EN), R10.2, U1.8 (EN/CHIP_PU)
GND: C1.2, C2.2, C3.2, C6.2, C7.2, C9.2, C10.2, C11.2, J1.1, J3.5 (GND), J4.1, Q1.2 (S), Q2.2 (S), Q3.2 (S), R1.2, R2.2, R3.2, R13.2, SW1.1, U1.1 (GND), U1.2 (GND), U1.11 (GND), U1.14 (GND), U1.36 (GND), U1.37 (GND), U1.38 (GND), U1.39 (GND), U1.40 (GND), U1.41 (GND), U1.42 (GND), U1.43 (GND), U1.44 (GND), U1.45 (GND), U1.46 (GND), U1.47 (GND), U1.48 (GND), U1.49 (GND), U1.50 (GND), U1.51 (GND), U1.52 (GND), U1.53 (GND), U2.2 (GND)
IO9: J3.2 (IO0/IO9), R7.2, SW1.2, U1.23 (GPIO9)
LED-B: R1.1, R5.1, U1.20 (GPIO6)
LED-G: R2.1, R4.1, U1.19 (GPIO5/ADC2_CH0)
LED-R: R3.1, R6.1, U1.18 (GPIO4/ADC1_CH4)
unnamed: J2.1, Q3.3 (D)
unnamed: J2.2, Q2.3 (D)
unnamed: J2.3, Q1.3 (D)
unnamed: Q1.1 (G), R6.2
unnamed: Q2.1 (G), R4.2
unnamed: Q3.1 (G), R5.2
unnamed: R8.2, U1.5 (GPIO2/ADC1_CH2)
unnamed: R9.2, U1.22 (GPIO8)
unnamed: C4.2, U2.1 (BS)
unnamed: R14.2, U2.4 (EN)
unnamed: C5.1, R12.2, R13.1, U2.3 (FB)
unnamed: C3.1, R11.2, R14.1, U2.5 (IN)
unnamed: C4.1, L1.1, U2.6 (LX)
RX: J3.4 (RX), U1.30 (GPIO20/U0RXD)
TX: J3.3 (TX), U1.31 (GPIO21/U0TXD)
USB-D+: J4.2, U1.27 (GPIO19/USB_D+)
USB-D-: J4.3, U1.26 (GPIO18/USB_D-)
